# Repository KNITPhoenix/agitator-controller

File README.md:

# agitator-controller (confidential)
agitator control for pcb

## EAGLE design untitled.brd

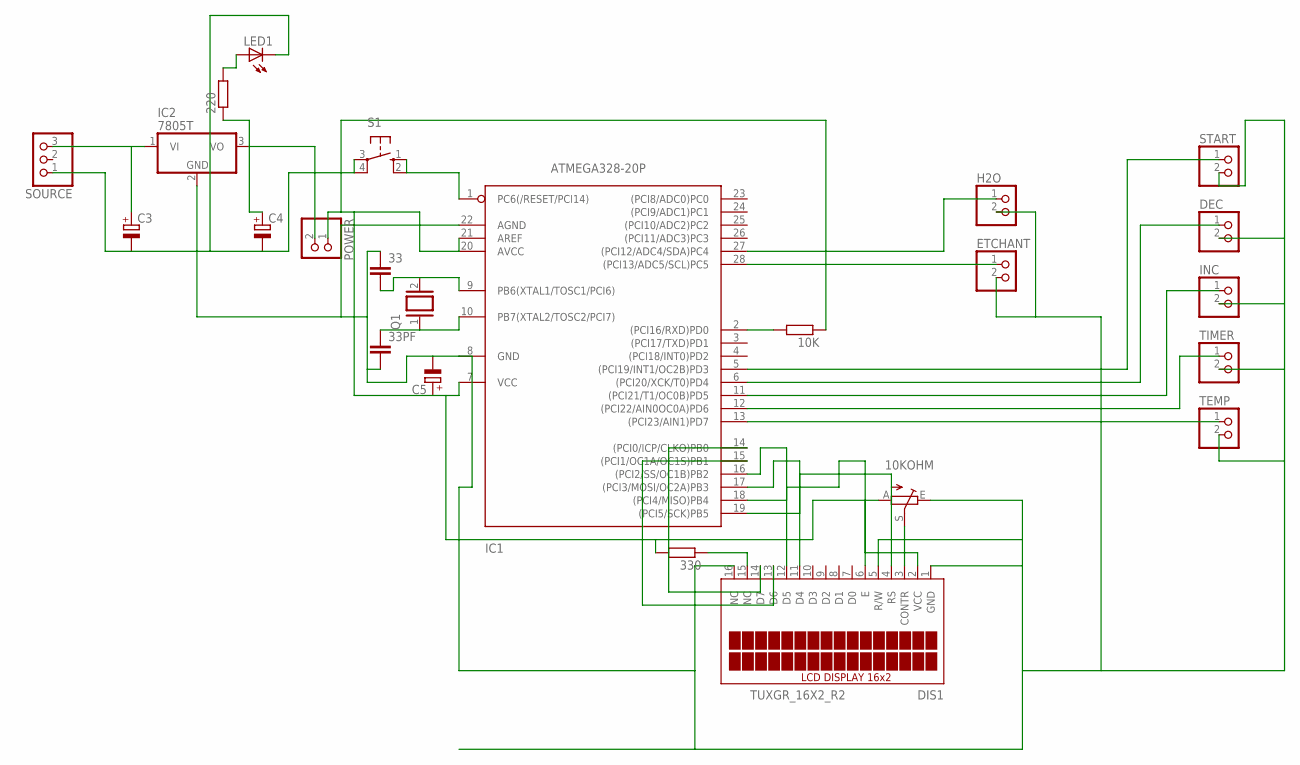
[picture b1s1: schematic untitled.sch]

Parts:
10K, 220, 330: R-EU_0204/7; 0204/7
10KOHM: TRIM_EU-CA6V; CA6V
33, 33PF: C-EU025-030X050; C025-030X050
C3, C4, C5: CPOL-EUE2.5-7; E2,5-7
DEC: PINHD-1X2; 1X02
DIS1: TUXGR_16X2_R2
ETCHANT: PINHD-1X2; 1X02
H2O: PINHD-1X2; 1X02
IC1: ATMEGA328-20P; DIL28-3
IC2: 7805T; TO220H
INC: PINHD-1X2; 1X02
LED1: LED_ELD260; LED_LD260
POWER: PINHD-1X2; 1X02
Q1: XTAL; Q
S1: 10-XX; B3F-10XX
SOURCE: PINHD-1X3; 1X03
START: PINHD-1X2; 1X02
TEMP: PINHD-1X2; 1X02
TIMER: PINHD-1X2; 1X02

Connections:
GND: 10KOHM.E, 33.1, 33PF.2, C3.-, C4.-, C5.-, DEC.2, DIS1.1 (GND), DIS1.5 (R/W), DIS1.16 (NC), ETCHANT.2, H2O.2, IC1.8 (GND), IC1.22 (AGND), IC2.2 (GND), INC.2, LED1.K (C), S1.3, S1.4 (P1), SOURCE.1, START.2, TEMP.2, TIMER.2
unnamed: C3.+, IC2.1 (VI), SOURCE.3
unnamed: 10KOHM.S, DIS1.3 (CONTR)
unnamed: 220.1, C4.+, IC2.3 (VO), POWER.2
unnamed: 220.2, LED1.A
unnamed: 33.2, IC1.9 (PB6(XTAL1/TOSC1/PCI6)), Q1.2
unnamed: 33PF.1, IC1.10 (PB7(XTAL2/TOSC2/PCI7)), Q1.1
unnamed: 10K.2, IC1.2 ((PCI16/RXD)PD0)
unnamed: 330.1, DIS1.15 (NC)
unnamed: DIS1.4 (RS), IC1.19 ((PCI5/SCK)PB5)
unnamed: DIS1.6 (E), IC1.18 ((PCI4/MISO)PB4)
unnamed: DIS1.11 (D4), IC1.17 ((PCI3/MOSI/OC2A)PB3)
unnamed: DIS1.12 (D5), IC1.16 ((PCI2/SS/OC1B)PB2)
unnamed: DIS1.13 (D6), IC1.15 ((PCI1/OC1A/OC1S)PB1)
unnamed: DIS1.14 (D7), IC1.14 ((PCI0/ICP/CLKO)PB0)
unnamed: IC1.13 ((PCI23/AIN1)PD7), TEMP.1
unnamed: IC1.12 ((PCI22/AIN0OC0A)PD6), TIMER.1
unnamed: IC1.11 ((PCI21/T1/OC0B)PD5), INC.1
unnamed: DEC.1, IC1.6 ((PCI20/XCK/T0)PD4)
unnamed: IC1.5 ((PCI19/INT1/OC2B)PD3), START.1
unnamed: ETCHANT.1, IC1.28 ((PCI13/ADC5/SCL)PC5)
unnamed: H2O.1, IC1.27 ((PCI12/ADC4/SDA)PC4)

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
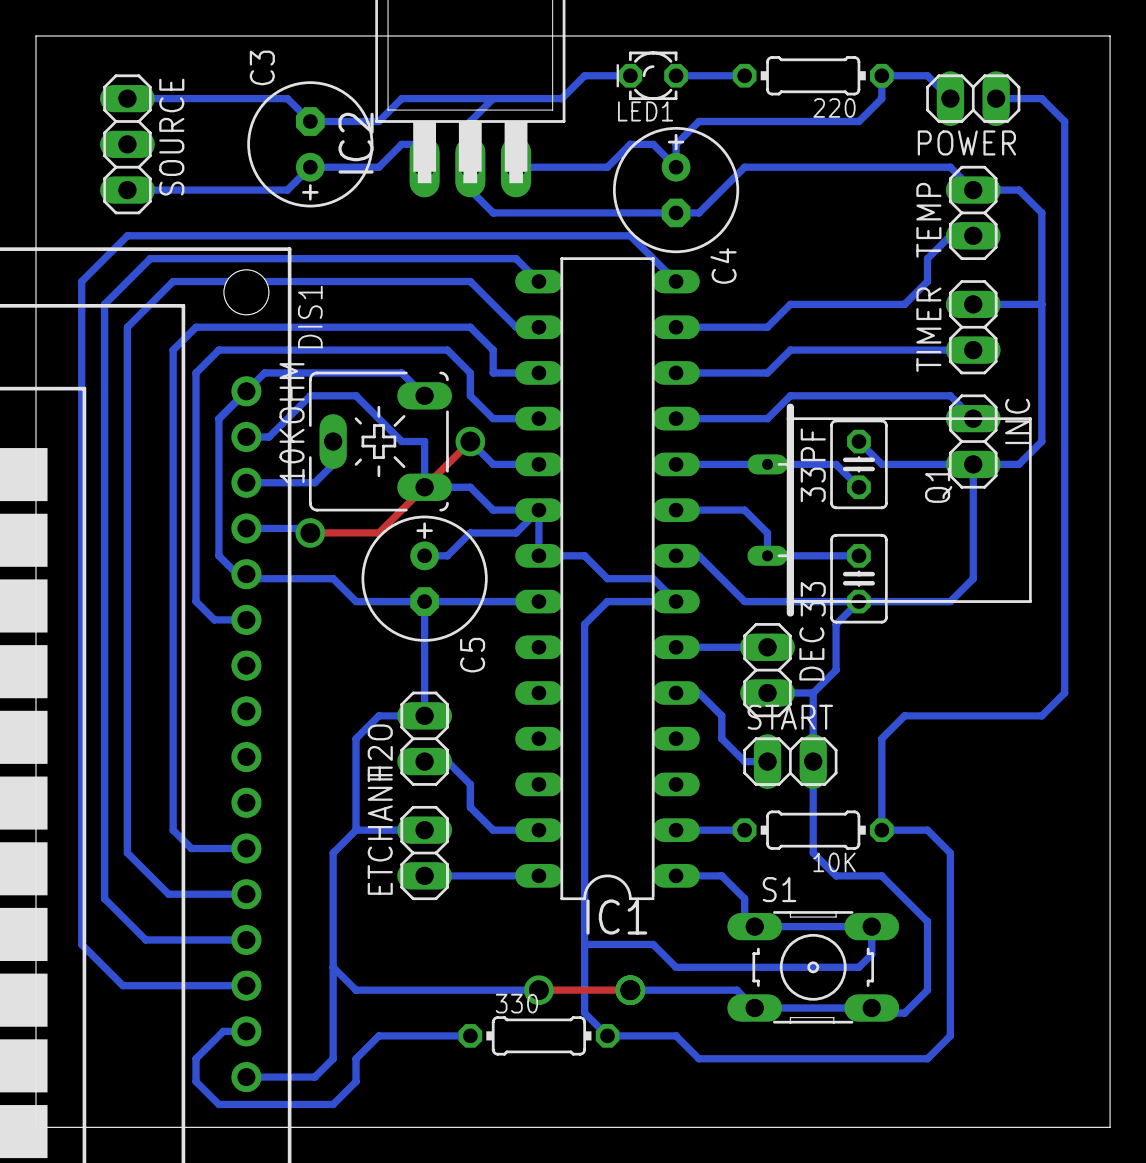
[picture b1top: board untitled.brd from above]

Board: 2 copper layers, 59.7 x 60.6 mm, 24 parts (0 on the bottom side), 23 nets.
